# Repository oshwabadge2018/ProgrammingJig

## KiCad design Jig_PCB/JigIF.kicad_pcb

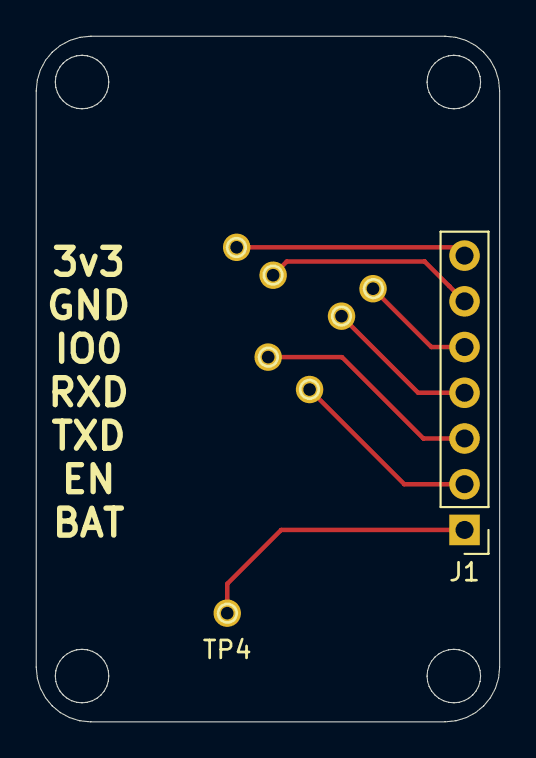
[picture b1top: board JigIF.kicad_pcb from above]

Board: 2 copper layers, 25.7 x 38.1 mm, 9 parts (0 on the bottom side), 7 nets.

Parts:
J1: Conn_01x07_Female; Socket_Strip_Straight_1x07_Pitch2.54mm
TP1, TP2, TP3, TP4, TP5, TP6, TP7: TestPoint; testpad_th
jig_footprint: G***; Jig_probe

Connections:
unnamed: J1.1, TP4.1
unnamed: J1.2, TP1.1
unnamed: J1.3, TP5.1
unnamed: J1.4, TP2.1
unnamed: J1.5, TP6.1
unnamed: J1.6, TP3.1
unnamed: J1.7, TP7.1

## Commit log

2018-08-04 Added Laser Cut Frame
2018-08-04 Probe PCB
2018-08-04 Jig Kicad PCB
2018-08-04 Updated gitignore
2018-08-18 badge step file
2018-08-18 test jig outlines dxf
2018-08-18 scaled DXF
2018-08-18 made .stl for jig in Blender
2018-08-18 gcode for jig
2018-09-23 ajustments to laser cut jig
2018-09-23 holder for screen
2018-09-23 board retaining clips
2018-09-23 adjusted text position
